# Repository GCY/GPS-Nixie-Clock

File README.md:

# GPS-Nixie-Clock

This is GPS Nixie clock,include IN12B, IN14, IN16, and IN2 version.</br>

## Firmware
### Parameter

__SERIAL__ : output info to serial port.</br>
DOT : use nixie tube dot.</br>
__GPS__ : time sync with Neo-6M - u-blox chip, this function only for IN14 IN16 version, and time sync separator is GPGGA[7] = {'$','G','P','G','G','A',','};</br>
<pre><code>
#define __SERIAL__ 1
#define DOT 1
#define __GPS__ 1
</code></pre>

gps_update : gps sync period, unit is ms, 300000ms = 5min.</br> 
<pre><code>
const unsigned long gps_update = 300000;
</code></pre>

Type select, IN_14 == IN_16.</br> 
<pre><code>
enum{
  IN_12B = 100,
  IN_14,
  IN_2
};
</code></pre>

<pre><code>
const bool sync_time = false; // sync time with Arduino IDE
const bool temperature_calibration = false; // offset
const bool dew_point = true;  // calculate dew point
</code></pre>
### Command

case '1' : clock mode
</br>
case '2' : temperature mode
</br>
case '3' : humidity mode
</br>
case '4' : flash mode
</br>
case '5' : counter mode
</br>
case '6' : '1' + '2' + '3'
</br>
case 's' | 'S' : set time
</br></br>

## Android time sync tool
Android App modified BlueTerm project. </br>

## PC Software - wxNixieClock
</br>
wxNixieClock is time sync tool for Nixie Clock project.(Only MAC-OS-X)</br>

### Build

g++ -o2 -o wxnixieclock.app wxnixieclock.cpp serialport.cpp connectargsdlg.cpp \`wx-config --cxxflags --libs\` -m64</br>
</br>
</br>

</br>
</br>

### Use
</br>
1. Pair BT of MAC and Nixie Clock.</br>
2. Open wxNixieClock to select tools -> Connect Device -> cu.BT device driver</br>
3. Click SyncTime button</br>
4. Done!</br>
</br>

### Dependency

</br>
Install wxWidgets dependency in terminal</br>
</br>
1. user$ /usr/bin/ruby -e "$(curl -fsSL https://raw.githubusercontent.com/Homebrew/install/master/install)" </br>
2. brew install wxwidgets </br>

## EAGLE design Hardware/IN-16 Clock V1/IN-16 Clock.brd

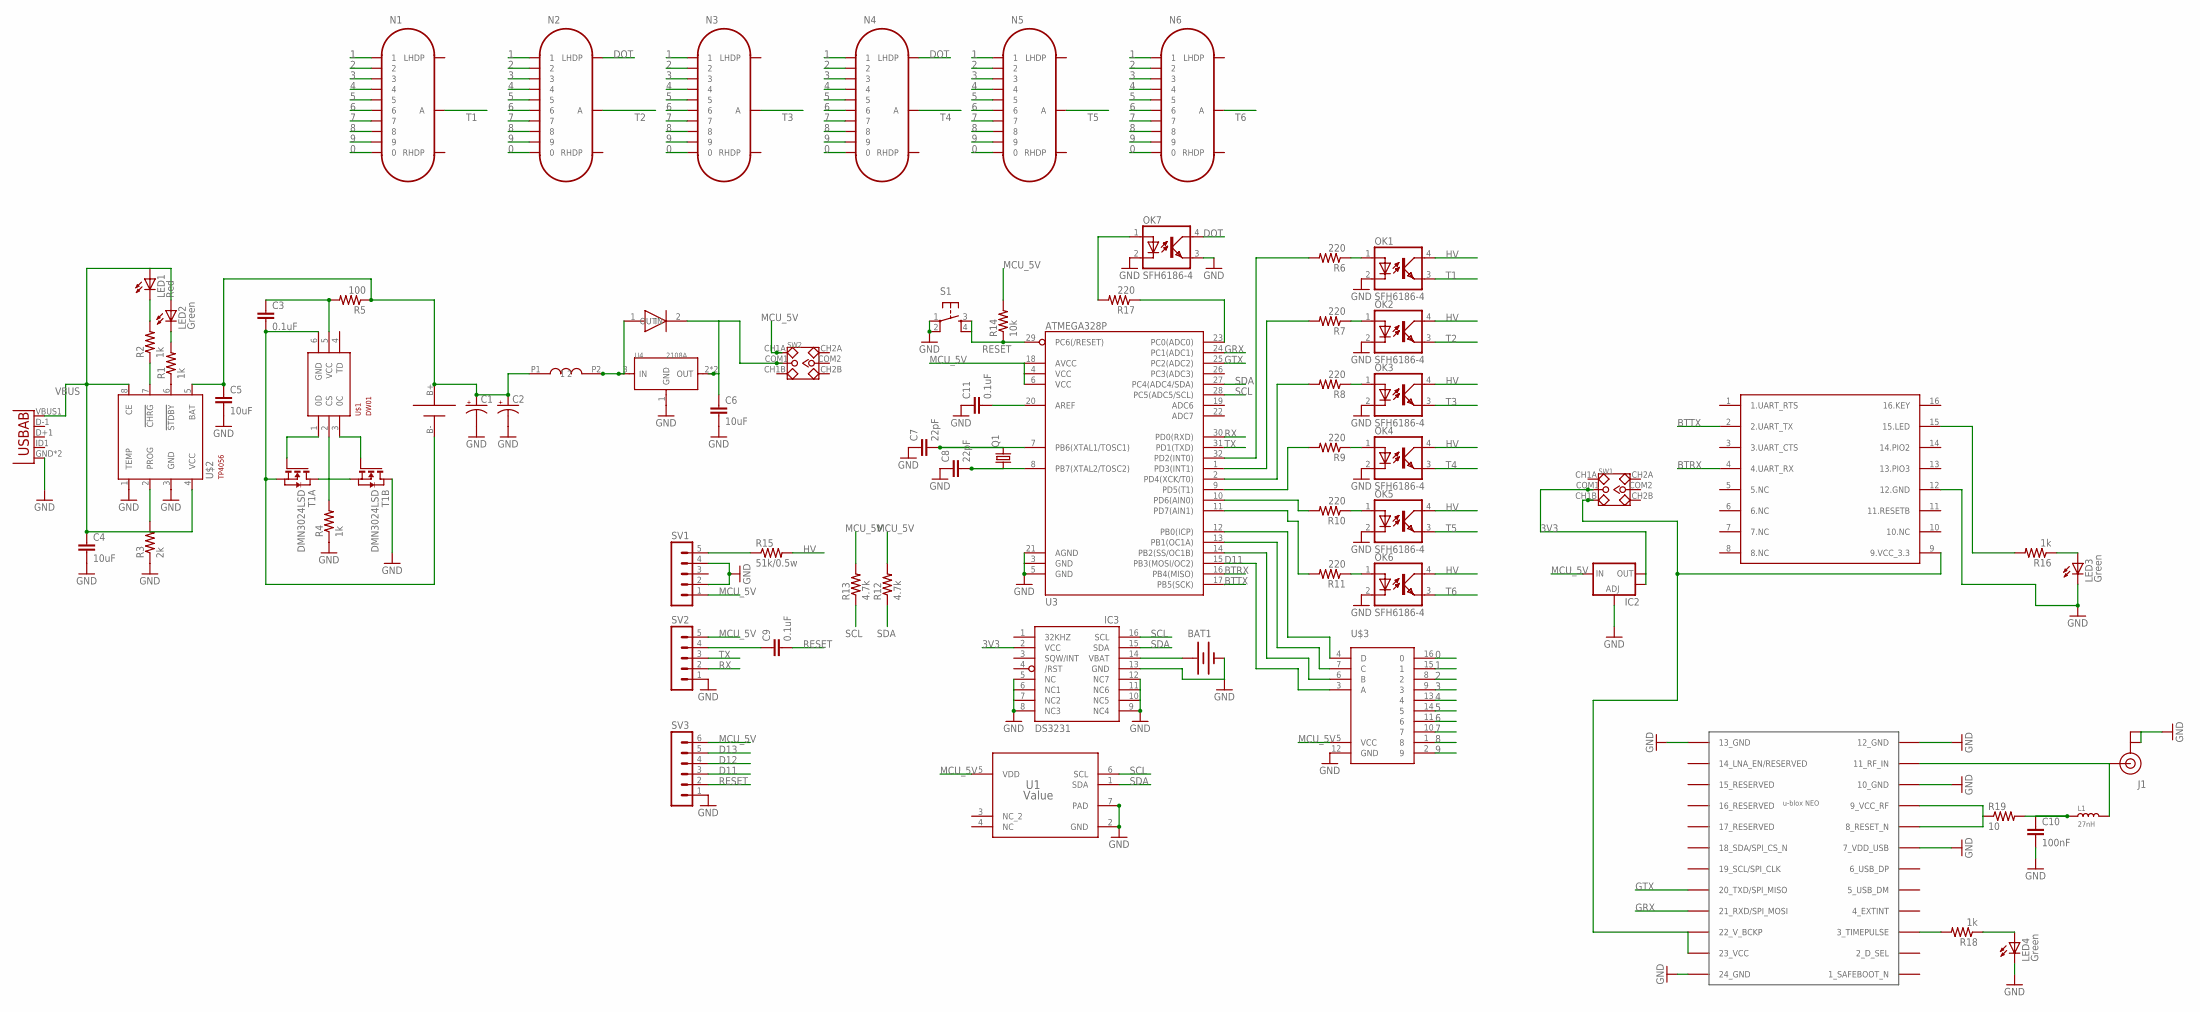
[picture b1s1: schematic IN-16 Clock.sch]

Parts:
BAT1: BATTERY20PTH; BATTCOM_20MM_PTH
C1, C2: CAP_POLF80; NIPPON_F80
C3, C9, C11: 0.1uF; 0603-CAP
C4, C5, C6: 10uF; 0603-CAP
C7, C8: 22pF; 0603-CAP
C10: 100nF; 0402-CAP
IC2: V_REG_LM1117SOT223; SOT223
IC3: DS3231/SO; SO16W
J1: U.FL
L1: 27nH; L0603
LED1: Red; CHIP-LED0805
LED2, LED3, LED4: Green; CHIP-LED0805
N1, N2, N3, N4, N5, N6: IN-16
OK1, OK2, OK3, OK4, OK5, OK6, OK7: SFH6186-4; SMD4-7
Q1: CRYSTALSM49; SM49
R1, R2, R4, R16, R18: 1k; 0603-RES
R3: 2k; 0603-RES
R5: 100; 0603-RES
R6, R7, R8, R9, R10, R11, R17: 220; 0603-RES
R12, R13: 4.7k; 0603-RES
R14: 10k; 0603-RES
R15: 51k/0.5w; 0207/12
R19: 10; 0603-RES
S1: TAC_SWITCHSMD; TACTILE_SWITCH_SMD
SV1, SV2: MA05-1
SV3: MA06-1
SW1, SW2: SMD-TOGGLE-SWITCH-2CH(2X3P-7X3.5MM); SW6-2.54-SMD-7.0X3.5X1.5MM
T1: DMN3024LSD; TSSOP-8
U1: Value; DMB0006A
U2: USB""; USB-MICRO-SMD
U3: ATMEGA328P; TQFP32-08
U4: 2108A; SOT-89
U$1: DW01; SOT23-6
U$2: TP4056; SOT23-8
U$3: K155ID1; DIL16-KIT
U$5: 22uH; CD54
U$6: SMA-SS34
U$7: 18650SMD
U$8: NEO-M8
U$9: HM-13

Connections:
0: N1.0, N2.0, N3.0, N4.0, N5.0, N6.0, U$3.16 (0)
1: N1.1, N2.1, N3.1, N4.1, N5.1, N6.1, U$3.15 (1)
2: N1.2, N2.2, N3.2, N4.2, N5.2, N6.2, U$3.8 (2)
3: N1.3, N2.3, N3.3, N4.3, N5.3, N6.3, U$3.9 (3)
3V3: IC2.2 (OUT), IC2.4 (OUT), IC3.2 (VCC), SW1.COM1
4: N1.4, N2.4, N3.4, N4.4, N5.4, N6.4, U$3.13 (4)
5: N1.5, N2.5, N3.5, N4.5, N5.5, N6.5, U$3.14 (5)
6: N1.6, N2.6, N3.6, N4.6, N5.6, N6.6, U$3.11 (6)
7: N1.7, N2.7, N3.7, N4.7, N5.7, N6.7, U$3.10 (7)
8: N1.8, N2.8, N3.8, N4.8, N5.8, N6.8, U$3.1 (8)
9: N1.9, N2.9, N3.9, N4.9, N5.9, N6.9, U$3.2 (9)
BTRX: U3.16 (PB4(MISO)), U$9.4 (4.UART_RX)
BTTX: U3.17 (PB5(SCK)), U$9.2 (2.UART_TX)
D11: SV3.3, U3.15 (PB3(MOSI/OC2)), U$3.3 (A)
D12: SV3.4
D13: SV3.5
DOT: N2.LHDP, N4.LHDP, OK7.4 (COL)
GND: BAT1.2 (-), C1.-, C2.-, C4.2, C5.2, C6.2, C7.1, C8.1, C10.2, C11.1, IC2.1 (ADJ), IC3.5 (NC), IC3.6 (NC1), IC3.7 (NC2), IC3.8 (NC3), IC3.9 (NC4), IC3.10 (NC5), IC3.11 (NC6), IC3.12 (NC7), IC3.13 (GND), J1.P$1 (GND), J1.P$2 (GND), LED3.C, LED4.C, OK1.2 (C), OK2.2 (C), OK3.2 (C), OK4.2 (C), OK5.2 (C), OK6.2 (C), OK7.2 (C), OK7.3 (EMIT), R3.1, R4.1, S1.1, S1.2, SV1.2, SV1.4, SV2.1, SV3.1, T1.8 (D), U1.2 (GND), U1.7 (PAD), U2.GND, U2.GND1 (GND), U3.3 (GND), U3.5 (GND), U3.21 (AGND), U4.1 (GND), U$2.1 (TEMP), U$2.3 (GND), U$3.12 (GND), U$8.7 (7_VDD_USB), U$8.10 (10_GND), U$8.12 (12_GND), U$8.13 (13_GND), U$8.24 (24_GND), U$9.12 (12.GND)
GRX: U3.24 (PC1(ADC1)), U$8.21 (21_RXD/SPI_MOSI)
GTX: U3.25 (PC2(ADC2)), U$8.20 (20_TXD/SPI_MISO)
HV: OK1.4 (COL), OK2.4 (COL), OK3.4 (COL), OK4.4 (COL), OK5.4 (COL), OK6.4 (COL), R15.2
MCU_5V: IC2.3 (IN), R12.2, R13.2, R14.2, SV1.1, SV2.5, SV3.6, SW2.CH1A, U1.5 (VDD), U3.4 (VCC), U3.6 (VCC), U3.18 (AVCC), U$3.5 (VCC)
unnamed: LED2.C, R1.2
unnamed: R1.1, U$2.6 (!STDBY)
unnamed: LED1.C, R2.2
unnamed: R2.1, U$2.7 (!CHRG)
unnamed: R3.2, U$2.2 (PROG)
unnamed: U4.3 (IN), U$5.P2 (2), U$6.1 (IN)
unnamed: C6.1, SW2.COM1, U4.2 (OUT), U4.4 (OUT), U$6.2 (OUT)
unnamed: T1.1 (D), T1.6 (S), T1.7 (S)
unnamed: T1.4 (G), U$1.1 (0D)
unnamed: T1.5 (G), U$1.3 (0C)
unnamed: R4.2, U$1.2 (CS)
unnamed: C3.2, T1.2 (S), T1.3 (S), U$1.6 (GND), U$7.B-
unnamed: C3.1, R5.2, U$1.5 (VCC)
unnamed: C1.+, C2.+, C5.1, R5.1, U$2.5 (BAT), U$5.P1 (1), U$7.B+
unnamed: C7.2, Q1.2, U3.7 (PB6(XTAL1/TOSC1))
unnamed: C8.2, Q1.1, U3.8 (PB7(XTAL2/TOSC2))
unnamed: BAT1.1 (+), IC3.14 (VBAT)
unnamed: C11.2, U3.20 (AREF)
unnamed: R15.1, SV1.5
unnamed: R18.2, U$8.3 (3_TIMEPULSE)
unnamed: LED4.A, R18.1
unnamed: OK1.1 (A), R6.1
unnamed: OK2.1 (A), R7.1
unnamed: OK3.1 (A), R8.1
unnamed: OK4.1 (A), R9.1
unnamed: OK5.1 (A), R10.1
unnamed: OK6.1 (A), R11.1
unnamed: R6.2, U3.32 (PD2(INT0))
unnamed: R7.2, U3.1 (PD3(INT1))
unnamed: R8.2, U3.2 (PD4(XCK/T0))
unnamed: R9.2, U3.9 (PD5(T1))
unnamed: R10.2, U3.10 (PD6(AIN0))
unnamed: R11.2, U3.11 (PD7(AIN1))
unnamed: U3.12 (PB0(ICP)), U$3.4 (D)
unnamed: U3.13 (PB1(OC1A)), U$3.7 (C)
unnamed: U3.14 (PB2(SS/OC1B)), U$3.6 (B)
unnamed: R17.1, U3.23 (PC0(ADC0))
unnamed: SW1.CH1B, U$8.22 (22_V_BCKP), U$8.23 (23_VCC), U$9.9 (9.VCC_3.3)
unnamed: OK7.1 (A), R17.2
unnamed: C9.1, SV2.4
unnamed: R16.2, U$9.15 (15.LED)
unnamed: LED3.A, R16.1
unnamed: C10.1, L1.1, R19.2
unnamed: R19.1, U$8.8 (8_RESET_N), U$8.9 (9_VCC_RF)
unnamed: J1.P$3 (SIGNAL), L1.2, U$8.11 (11_RF_IN)
RESET: C9.2, R14.1, S1.3, S1.4, SV3.2, U3.29 (PC6(/RESET))
RX: SV2.2, U3.30 (PD0(RXD))
SCL: IC3.16 (SCL), R13.1, U1.6 (SCL), U3.28 (PC5(ADC5/SCL))
SDA: IC3.15 (SDA), R12.1, U1.1 (SDA), U3.27 (PC4(ADC4/SDA))
T1: N1.A, OK1.3 (EMIT)
T2: N2.A, OK2.3 (EMIT)
T3: N3.A, OK3.3 (EMIT)
T4: N4.A, OK4.3 (EMIT)
T5: N5.A, OK5.3 (EMIT)
T6: N6.A, OK6.3 (EMIT)
TX: SV2.3, U3.31 (PD1(TXD))
VBUS: C4.1, LED1.A, LED2.A, U2.VBUS1 (VBUS), U$2.4 (VCC), U$2.8 (CE)

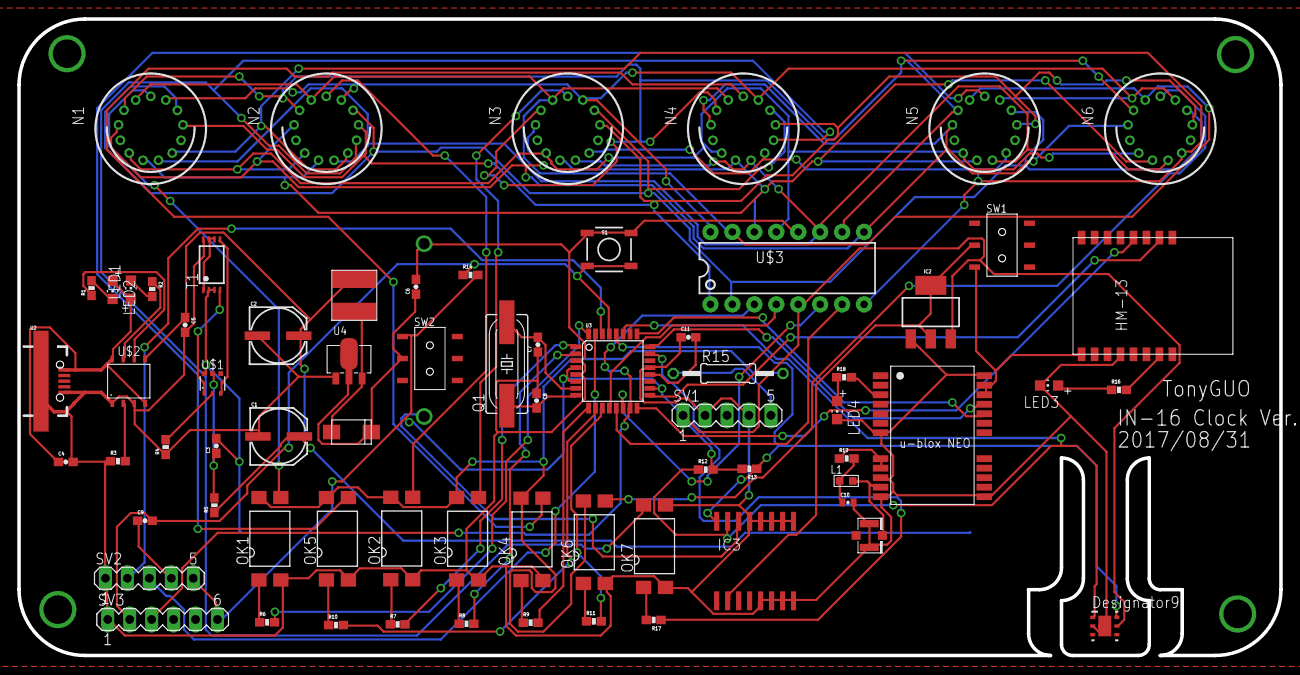
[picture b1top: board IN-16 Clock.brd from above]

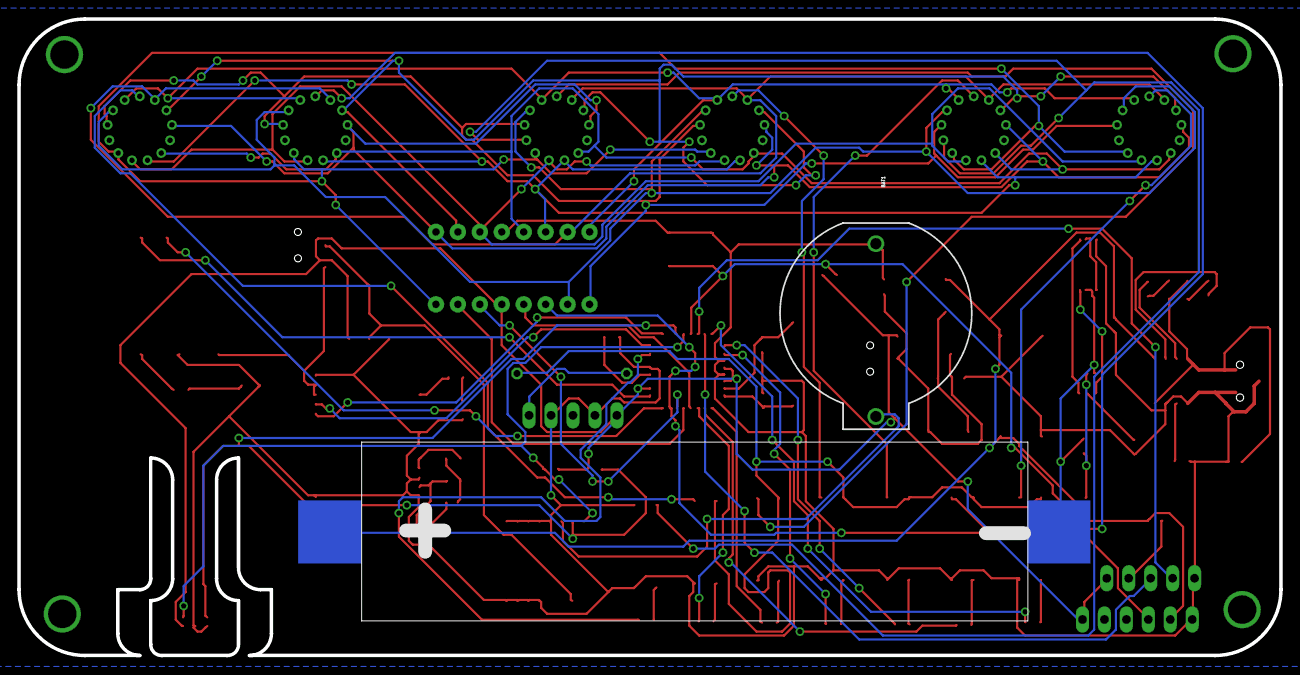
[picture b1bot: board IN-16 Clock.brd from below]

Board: 2 copper layers, 146.0 x 73.7 mm, 72 parts (2 on the bottom side), 77 nets.

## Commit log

2017-08-01 Hardware
2017-08-01 Software
2017-09-02 IN-2
2018-04-24 GPS NMEA-0183 date parse
2018-04-24 edited version from https://github.com/johnhowe/BlueTerm
2018-09-08 Time Sync Tools for MAC OS X
2019-12-20 picture
2019-12-20 IN-16 version
2019-12-30 Add HDC1080 Dew Point
2021-10-14 edit

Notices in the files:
parts and their libraries:
SparkFun-DigitalIC: Licensing: CC v3.0 Share-Alike You are welcome to use this library for commercial purposes.
